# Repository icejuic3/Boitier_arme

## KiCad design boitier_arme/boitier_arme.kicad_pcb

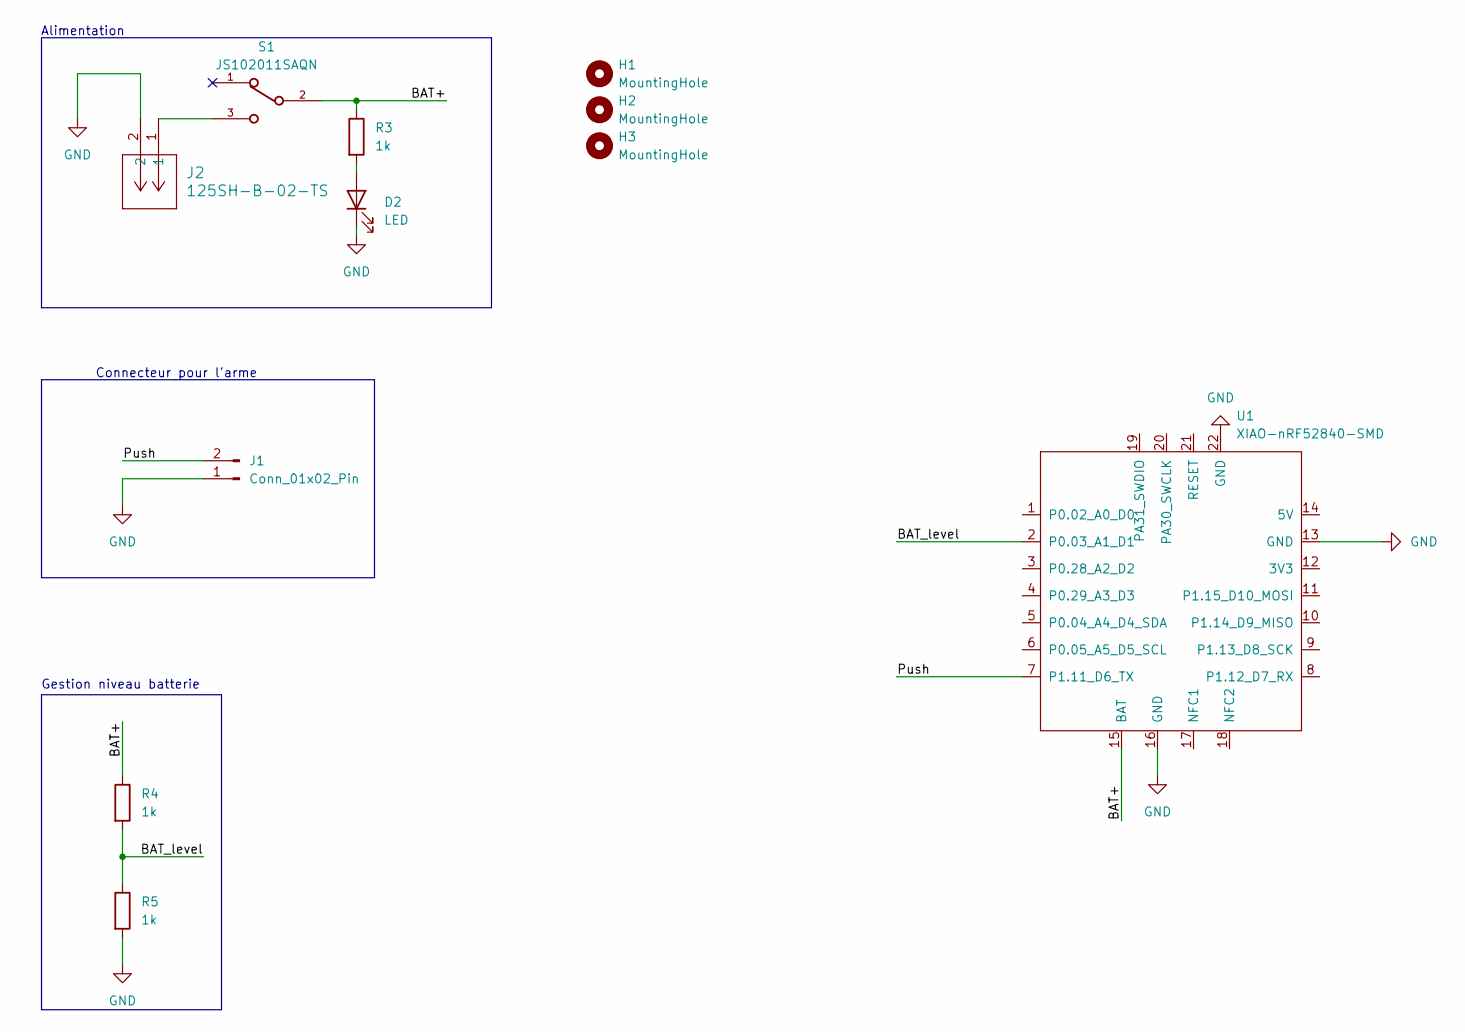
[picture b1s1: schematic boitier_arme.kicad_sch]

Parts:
D2: LED; LED_D5.0mm
H1, H2, H3: MountingHole; MountingHole_3.5mm
J1: Conn_01x02_Pin; JST_XH_S2B-XH-A-1_1x02_P2.50mm_Horizontal
J2: 125SH-B-02-TS; CONN_125SH-B-02-TS_ADM
R3, R4, R5: 1k; R_Axial_DIN0204_L3.6mm_D1.6mm_P2.54mm_Vertical
S1: JS102011SAQN; SW_SPDT_CK_JS102011SAQN
U1: XIAO-nRF52840-SMD

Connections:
/BAT+: R3.1, R4.1, S1.2, U1.15 (BAT)
/BAT_level: R4.2, R5.1, U1.2 (P0.03_A1_D1)
/Push: J1.2, U1.7 (P1.11_D6_TX)
GND: D2.1 (K), J1.1, J2.2, R5.2, U1.13 (GND), U1.16 (GND), U1.22 (GND)
unnamed: D2.2 (A), R3.2
unnamed: J2.1, S1.3

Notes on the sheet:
Connecteur pour l'arme
Alimentation
Gestion niveau batterie

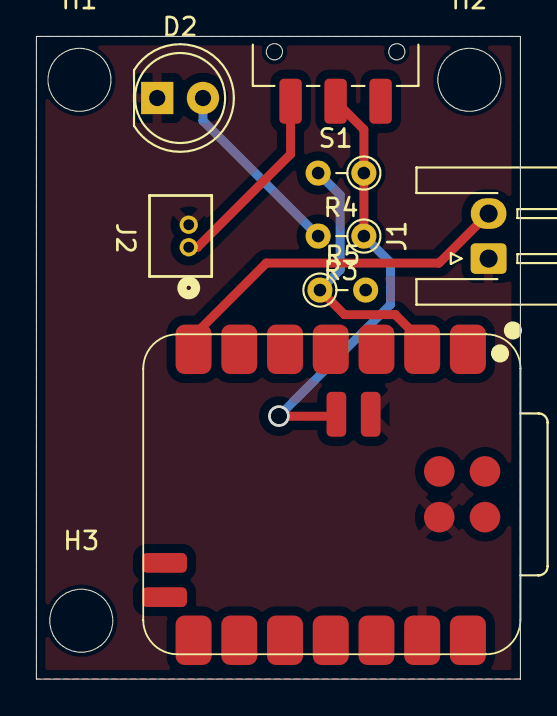
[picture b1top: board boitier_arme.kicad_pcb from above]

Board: 2 copper layers, 26.9 x 35.7 mm, 11 parts (0 on the bottom side), 6 nets.

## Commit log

2025-07-14 a verifier
2025-07-15 batterie rajouté
2025-07-15 a jour
2025-07-17 Changement suite au retour du GUS
